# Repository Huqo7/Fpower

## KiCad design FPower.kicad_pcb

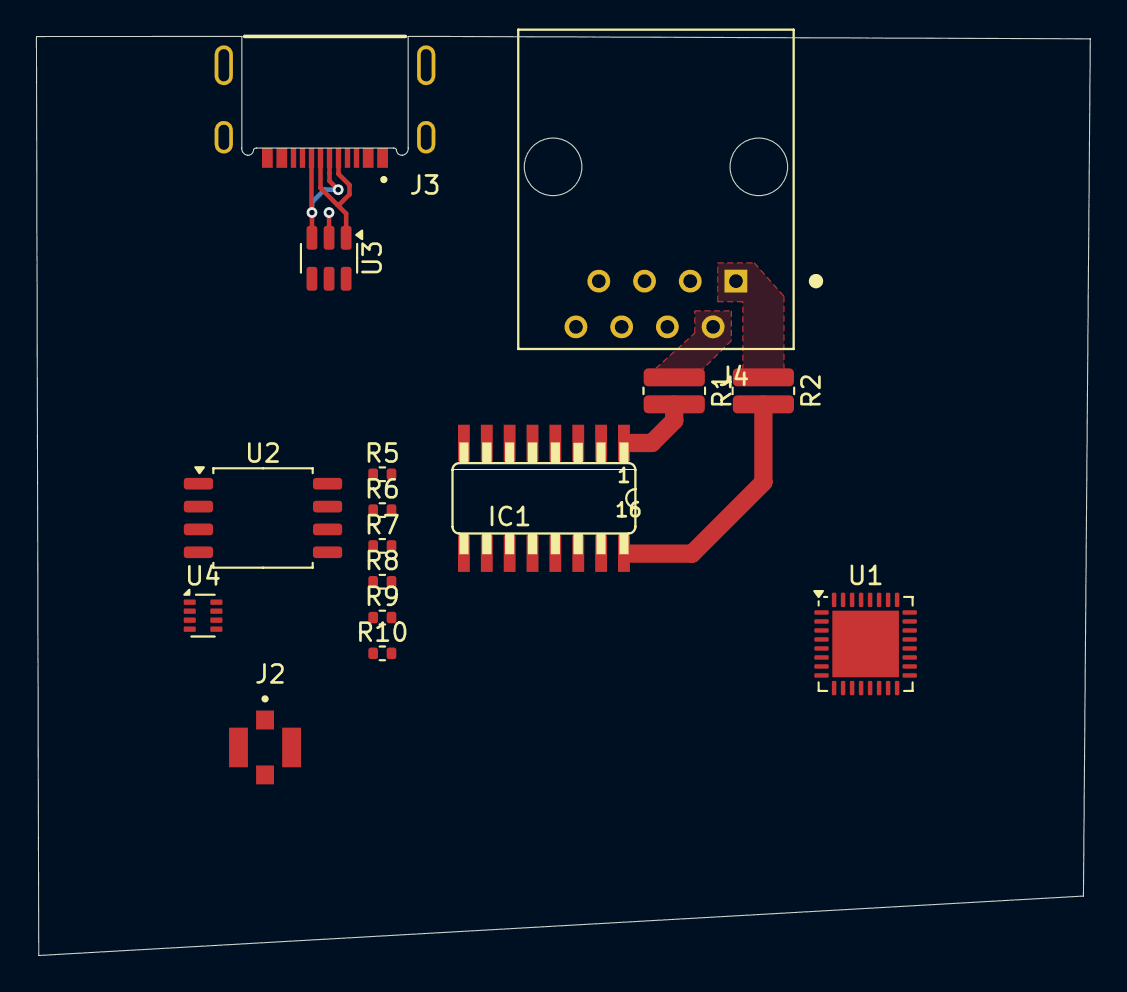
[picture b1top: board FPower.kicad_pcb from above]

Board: 2 copper layers, 58.5 x 51.1 mm, 16 parts (0 on the bottom side), 28 nets.

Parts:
IC1: TSS721; SO16
J2: CONMHF1-SMD-G-T; LINX_CONMHF1-SMD-G-T
J3: USB4520-03-0-A_REVA; GCT_USB4520-03-0-A_REVA
J4: 54602-908LF; AMPHENOL_54602-908LF
R1, R2: 220R; R_0612_1632Metric
R5, R6, R7, R8, R9, R10: 0R; R_0402_1005Metric
U1: ESP32-C3; QFN-32-1EP_5x5mm_P0.5mm_EP3.7x3.7mm
U2: W25Q16JVSS; SOIC-8_5.3x5.3mm_P1.27mm
U3: USBLC6-2SC6; SOT-23-6
U4: TPS2116DRL; SOT-583-8

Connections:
/DN: J3.A7 (DN1), J3.B7 (DN2), U3.1 (I/O1)
/DN_P: U1.25 (GPIO18), U3.6 (I/O1)
/DP: J3.A6 (DP1), J3.B6 (DP2), U3.3 (I/O2)
/DP_P: U1.26 (GPIO19), U3.4 (I/O2)
/RXI: IC1.13 (RXI), U1.28 (U0TXD)
/SPICLK: R6.1, U1.22 (SPICLK)
/SPICS0: R5.1, U1.21 (SPICS0)
/SPID: R7.1, U1.23 (SPID)
/SPIHD: R10.1, U1.19 (SPIHD)
/SPIQ: R8.1, U1.24 (SPIQ)
/SPIWP: R9.1, U1.20 (SPIWP)
/TXI: IC1.7 (TXI), U1.27 (U0RXD)
GND: IC1.15 (GND), J2.S1, J2.S2, J2.S3, J3.A1_B12 (GND_A), J3.B1_A12 (GND_B), J3.S1 (SHELL_GND), J3.S2 (SHELL_GND__1), J3.S3 (SHELL_GND__2), J3.S4 (SHELL_GND__3), U1.33 (GND), U2.4 (GND), U3.2 (GND), U4.1 (GND)
unnamed: U1.2 (VDD3P3), U1.3 (VDD3P3)
unnamed: IC1.16 (BUS1), R2.2
unnamed: IC1.1 (BUS2), R1.2
unnamed: J4.1, R2.1
unnamed: J4.2, R1.1
unnamed: R6.2, U2.6 (CLK)
unnamed: R7.2, U2.5 (DI/IO_{0})
unnamed: R8.2, U2.2 (DO/IO_{1})
unnamed: R5.2, U2.1 (~CS)
unnamed: R10.2, U2.7 (~HOLD/~RESET/IO_{3})
unnamed: R9.2, U2.3 (~WP/IO_{2})
VDD: U1.11 (VDD3P3_RTC), U1.17 (VDD3P3_CPU), U1.31 (VDDA), U1.32 (VDDA), U4.2 (VOUT), U4.7 (VOUT)
VDD_MBUS: IC1.9 (BAT), IC1.11 (VDD), U4.3 (VIN1), U4.5 (MODE)
VDD_SPI: U1.18 (VDD_SPI), U2.8 (VCC)
VDD_USB: J3.A4_B9 (VBUS_A), J3.B4_A9 (VBUS_B), U3.5 (VBUS), U4.6 (VIN2)

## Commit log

2025-06-06 Initial Project
2025-06-08 updated component values
